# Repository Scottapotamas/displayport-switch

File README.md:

# DisplayPort Switch

Simple board to provide DisplayPort >1.2 source selection control.

While not explicitly designed for a particular direction, the intent is usage with 2 video sources (different computers) and a single sink (one monitor).

## Notes

- Switching is provided externally through the header.
- As this board is a prototype, there's no guarantee of stability or reliability.

- The planned enclosure method is to wrap the board with heatshrink and let it 'hang' in the display cable bundle.

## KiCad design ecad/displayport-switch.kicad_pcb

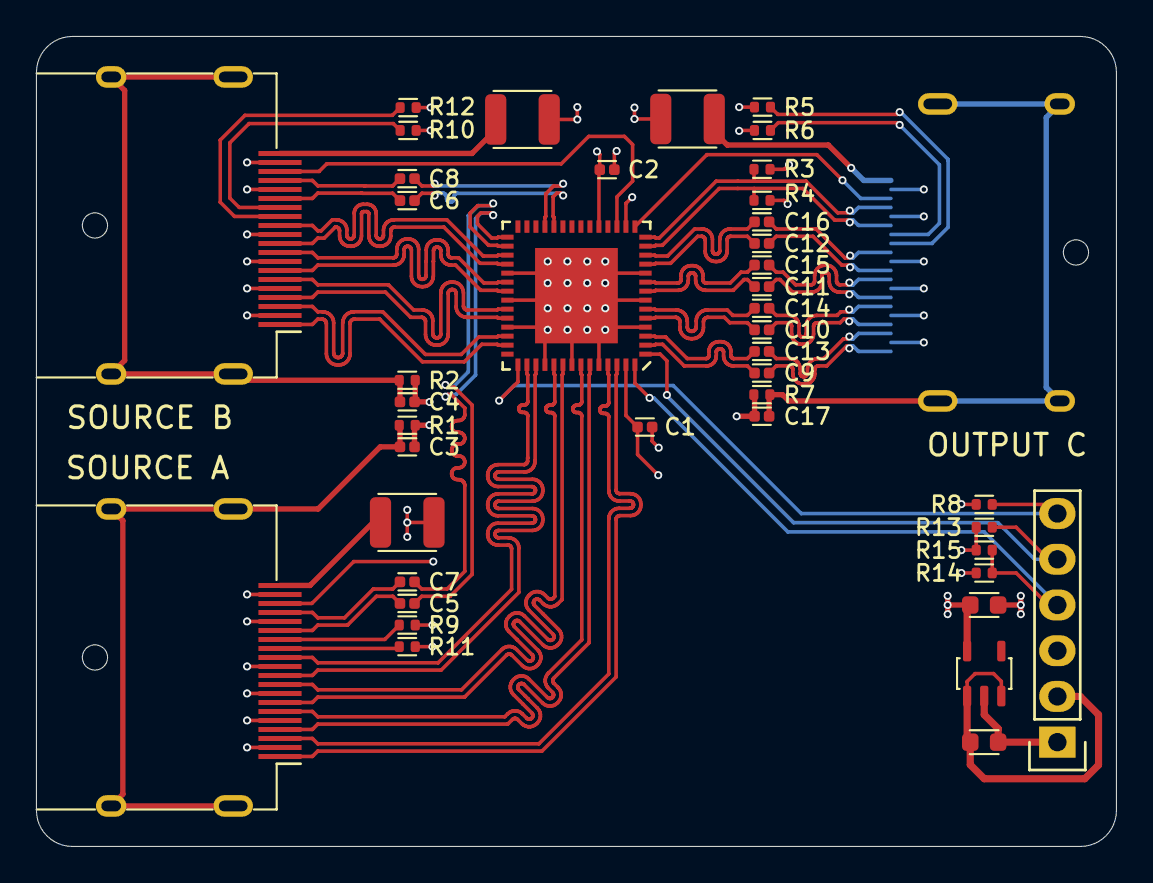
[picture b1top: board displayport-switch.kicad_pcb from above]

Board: 4 copper layers, 60.0 x 45.0 mm, 43 parts (1 on the bottom side), 63 nets.

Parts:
C1, C2, C5, C6, C7, C8, C9, C10, C11, C12, C13, C14, C15, C16: 100n_X7R_1005M; CAPC1005X60N
C3, C4, C17: 1u_X5R_1005M; CAPC1005X60N
C18, C19: 4u7_X5R_1608M; CAPC1608X90N
F1, F2, F3: 0.5A_1210L_PTC; FUSC3225X85L50N
P1, P2, P3: MOLEX_47272-0001
P5: CONN_01X06; 61300611121
R1, R2, R5, R6, R7, R9, R10, R11, R12: 1M_1005M; RESC1005X40N
R3, R4, R14, R15: 100K_1005M; RESC1005X40N
R8, R13: 10K0_1005M; RESC1005X40N
U1: HD3SS215IRTQT; QFN50P800x800x090-56T560x560N
U2: AP2112K-3.3; SOT95P280X145-5L30N

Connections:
+3.3V: C1.2, C2.1, C19.1, F1.2, F2.2, F3.2, P5.3, R3.1, R8.1, R14.1, U1.19, U1.55, U2.5
+5V: C18.1, P5.2, U2.1, U2.3
/AUXA+: C5.1, U1.30
/AUXA-: C7.1, U1.29
/AUXB+: C6.1, U1.24
/AUXB-: C8.1, U1.25
/AUXC+: P3.15, R4.1, U1.13
/AUXC-: P3.17, R3.2, U1.14
/DA0+: P1.1, U1.54
/DA0-: P1.3, U1.53
/DA1+: P1.4, U1.51
/DA1-: P1.6, U1.50
/DA2+: P1.7, U1.48
/DA2-: P1.9, U1.47
/DA3+: P1.10, U1.45
/DA3-: P1.12, U1.44
/DB0+: P2.1, U1.41
/DB0-: P2.3, U1.40
/DB1+: P2.4, U1.38
/DB1-: P2.6, U1.37
/DB2+: P2.7, U1.35
/DB2-: P2.9, U1.34
/DB3+: P2.10, U1.32
/DB3-: P2.12, U1.31
/DC0+: C9.2, U1.2
/DC0-: C13.2, U1.3
/DC1+: C10.2, U1.5
/DC1-: C14.2, U1.6
/DC2+: C11.2, U1.8
/DC2-: C15.2, U1.9
/DC3+: C12.2, U1.11
/DC3-: C16.2, U1.12
/_AUXA+: C5.2, P1.15
/_AUXA-: C7.2, P1.17
/_AUXB+: C6.2, P2.15
/_AUXB-: C8.2, P2.17
/_DC0+: C9.1, P3.1
/_DC0-: C13.1, P3.3
/_DC1+: C10.1, P3.4
/_DC1-: C14.1, P3.6
/_DC2+: C11.1, P3.7
/_DC2-: C15.1, P3.9
/_DC3+: C12.1, P3.10
/_DC3-: C16.1, P3.12
AUX_SEL: P5.5, R13.1, U1.1
ENABLE: P5.6, R8.2, U1.43
GND: C1.1, C2.2, C3.2, C4.2, C17.2, C18.2, C19.2, P1.2, P1.5, P1.8, P1.11, P1.16, P1.19, P2.2, P2.5, P2.8, P2.11, P2.16, P2.19, P3.2, P3.5, P3.8, P3.11, P3.16, P3.19, P5.1, R1.1, R2.1, R4.2, R5.1, R6.2, R7.1, R9.1, R10.1, R11.2, R12.2, R13.2, R15.2, U1.4, U1.7, U1.10, U1.33, U1.36, U1.39, U1.46, U1.49, U1.52, U1.57, U2.2
INPUT_SELECT: P5.4, R14.2, R15.1, U1.56
unnamed: C3.1, P1.SH, R1.2
unnamed: C4.1, P2.SH, R2.2
unnamed: C17.1, P3.SH, R7.2
unnamed: F1.1, P1.20
unnamed: F2.1, P2.20
unnamed: F3.1, P3.20
unnamed: P1.13, R11.1
unnamed: P1.14, R9.2
unnamed: P1.18, U1.16
unnamed: P2.13, R12.1
unnamed: P2.14, R10.2
unnamed: P2.18, U1.17
unnamed: P3.13, R5.2
unnamed: P3.14, R6.1
unnamed: P3.18, U1.15

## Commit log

2021-01-06 Initial chematic capture
2021-01-06 Partial routing concepts
2021-01-07 HS routing done?
2021-01-07 Routing/Layout completed, cosmetics
2021-01-21 Add basic README info and img
